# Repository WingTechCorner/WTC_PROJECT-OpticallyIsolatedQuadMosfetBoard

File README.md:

# OpticallyIsolatedQuadMosfetBoard

PCB Board designed to control 4 optically isolated MOSFETS via an ESP32 module

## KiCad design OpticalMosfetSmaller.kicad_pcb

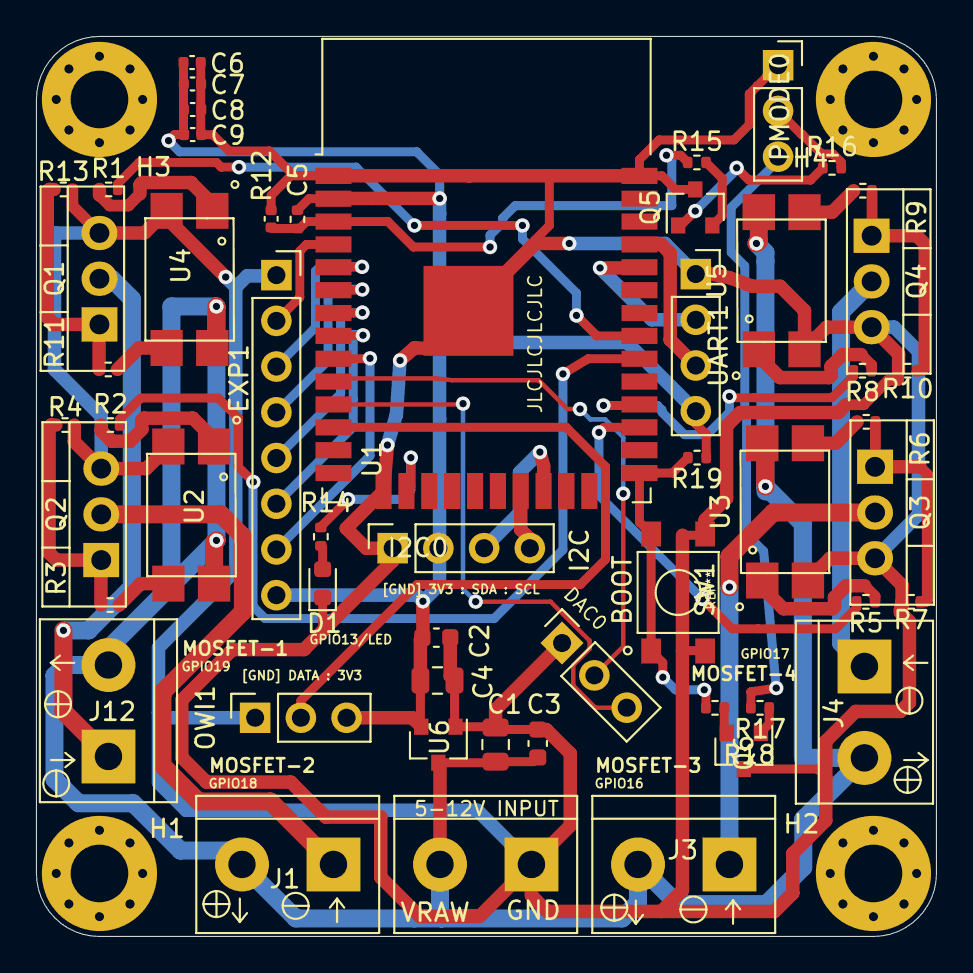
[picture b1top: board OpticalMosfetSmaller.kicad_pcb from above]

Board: 2 copper layers, 50.0 x 50.0 mm, 57 parts (0 on the bottom side), 46 nets.

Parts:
C1, C4: 10uF-25V-0805; C_0805_2012Metric
C2, C3: 100nF-50V-0603; C_0603_1608Metric
C5, C8, C9: 100nF-16V-0402; C_0402_1005Metric
C6, C7: 10nF-50V-0402; C_0402_1005Metric
D1: BLUE_LED; D_0603_1608Metric
DAC0: Conn_01x03; PinSocket_1x03_P2.54mm_Vertical
EXP1: Conn_01x08_Female; PinSocket_1x08_P2.54mm_Vertical
H1, H2, H3, H4: MountingHole; MountingHole_3.2mm_M3_Pad_Via
I2C0: Conn_01x04_Male; PinSocket_1x04_P2.54mm_Vertical
J1, J3, J4, J12: Screw_Terminal_01x02_K301_5mm; TerminalBlock_bornier-2_P5.08mm
OWI1: Conn_01x03; PinSocket_1x03_P2.54mm_Vertical
PMODE0: Conn_01x03; PinSocket_1x03_P2.54mm_Vertical
PWR1: Screw_Terminal_01x02_K301_5mm; TerminalBlock_bornier-2_P5.08mm
Q1, Q2, Q3, Q4: IRF540N; TO-220-3_Vertical
Q5, Q6: Q_NPN_S9013; SOT-23
R1, R2, R3, R5, R6, R8, R9, R11: 100Ohms-±1%-1_16W-0402; R_0402_1005Metric
R4, R7, R10, R13: 39KOhms-±1%-1_16W-0402; R_0402_1005Metric
R12, R16, R17, R19: 10KOhms-±1%-1_16W-0402; R_0402_1005Metric
R14: 47Ohms-±1%-1_16W-0402; R_0402_1005Metric
R15, R18: 1KOhms-±1%-1_16W-0402; R_0402_1005Metric
SW1: SW-Tactile-4.5x4.5_7mm; SMT-SW-SPST-4.5x4.5_plain
U1: ESP32-WROOM-32D; ESP32-WROOM-32
U2, U3, U4, U5: EL817S1; SMD-4_4.6x6.5x2.54P
U6: XC6206-vreg; SOT-23
UART1: Conn_01x04_Male; PinSocket_1x04_P2.54mm_Vertical

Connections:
1WIREDATA: OWI1.2, U1.12
3V3: C2.2, C4.1, C6.1, C7.1, C8.1, C9.1, EXP1.8, I2C0.2, OWI1.3, R12.1, R19.1, U1.2, U6.2, UART1.4
/AllOptoMosfetModules/sheet600F9CED/DRAIN: J1.1, Q2.2
/AllOptoMosfetModules/sheet600F9CED/GATE: Q2.1, R3.1, R4.1
/AllOptoMosfetModules/sheet600F9E4E/DRAIN: J3.1, Q3.2
/AllOptoMosfetModules/sheet600F9E4E/GATE: Q3.1, R6.1, R7.1
/AllOptoMosfetModules/sheet600F9F0D/DRAIN: J4.1, Q4.2
/AllOptoMosfetModules/sheet600F9F0D/GATE: Q4.1, R9.1, R10.1
/AllOptoMosfetModules/sheet60052ED4/DRAIN: J12.1, Q1.2
/AllOptoMosfetModules/sheet60052ED4/GATE: Q1.1, R11.1, R13.1
/BOOT: R18.1, R19.2, SW1.1, U1.25
/EN: C5.1, R12.2, R15.1, U1.3
BOOT-SIG: PMODE0.3, R17.2
DAC1: DAC0.2, U1.10
DAC2: DAC0.3, U1.11
EN-SIG: PMODE0.2, R16.2
EXT1: EXP1.2, U1.4
EXT2: EXP1.3, U1.5
EXT3: EXP1.4, U1.6
EXT4: EXP1.5, U1.7
EXT5: EXP1.6, U1.8
EXT6: EXP1.7, U1.9
GND: C1.1, C2.1, C3.2, C4.2, C5.2, C6.2, C7.2, C8.2, C9.2, D1.1, DAC0.1, EXP1.1, I2C0.1, OWI1.1, PMODE0.1, PWR1.1, Q1.3, Q2.3, Q3.3, Q4.3, Q5.3, Q6.3, R4.2, R7.2, R10.2, R13.2, SW1.2, U1.1, U1.15, U1.38, U1.39, U2.2, U3.2, U4.2, U5.2, U6.1, UART1.1
unnamed: D1.2, R14.1
unnamed: Q5.1, R16.1
unnamed: Q5.2, R15.2
unnamed: Q6.1, R17.1
unnamed: Q6.2, R18.2
unnamed: R1.1, U4.1
unnamed: R2.1, U2.1
unnamed: R3.2, U2.3
unnamed: R5.1, U3.1
unnamed: R6.2, U3.3
unnamed: R8.1, U5.1
unnamed: R9.2, U5.3
unnamed: R11.2, U4.3
unnamed: R14.2, U1.16
RXD: U1.34, UART1.2
SCL: I2C0.4, U1.21
SDA: I2C0.3, U1.22
SIG1: R1.2, U1.31
SIG2: R2.2, U1.30
SIG3: R5.2, U1.27
SIG4: R8.2, U1.28
TXD: U1.35, UART1.3
VRAW: C1.2, C3.1, J1.2, J3.2, J4.2, J12.2, PWR1.2, U2.4, U3.4, U4.4, U5.4, U6.3

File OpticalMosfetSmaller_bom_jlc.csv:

"Comment","Designator","Footprint","LCSC Part #"
"100nF-50V-0603","C3,C2","C_0603_1608Metric","C14663"
"10uF-25V-0805","C4,C1","C_0805_2012Metric","C15850"
"100nF-16V-0402","C5,C8,C9","C_0402_1005Metric","C1525"
"10nF-50V-0402","C7,C6","C_0402_1005Metric","C15195"
"BLUE_LED","D1","D_0603_1608Metric","C72041"
"Q_NPN_S9013","Q5,Q6","SOT-23","C6749"
"100Ohms-±1%-1_16W-0402","R11,R1,R3,R2,R6,R5,R9,R8","R_0402_1005Metric","C25076"
"10KOhms-±1%-1_16W-0402","R12,R16,R17,R19","R_0402_1005Metric","C25744"
"39KOhms-±1%-1_16W-0402","R13,R4,R7,R10","R_0402_1005Metric","C25783"
"47Ohms-±1%-1_16W-0402","R14","R_0402_1005Metric","C25118"
"1KOhms-±1%-1_16W-0402","R15,R18","R_0402_1005Metric","C11702"
"SW-Tactile-4.5x4.5_7mm","SW1","SMT-SW-SPST-4.5x4.5_plain","C480315"
"ESP32-WROOM-32D","U1","ESP32-WROOM-32","C473012"
"EL817S1","U4,U2,U3,U5","SMD-4_4.6x6.5x2.54P","C106900"
"XC6206-vreg","U6","SOT-23","C5446"

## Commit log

2021-06-03 Adding prod zip files
2021-06-03 Adding CSV, DRL, PRO, and SCH files
2021-06-03 Image

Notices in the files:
OpticalMosfetSmaller.kicad_pcb:
(C)2021 Wing Tang Wong
